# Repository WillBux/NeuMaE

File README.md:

# NeuMaE
Cue Stick for Neuromakers

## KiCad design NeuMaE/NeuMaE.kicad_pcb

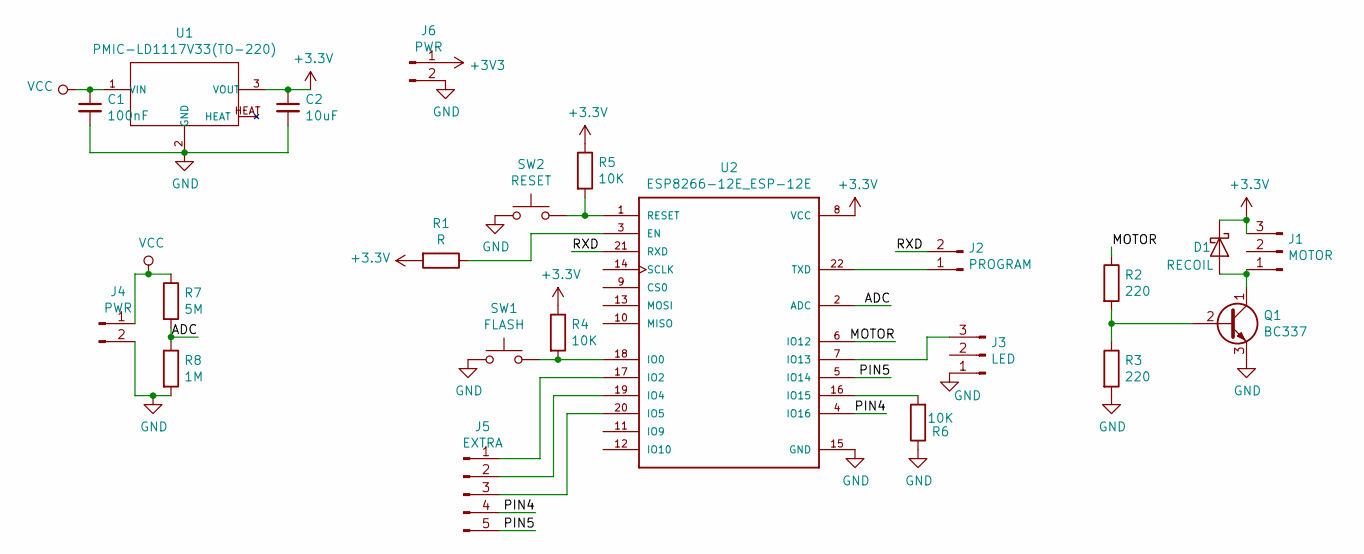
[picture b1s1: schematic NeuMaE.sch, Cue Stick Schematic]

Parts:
C1: 100nF; C_Rect_L7.2mm_W2.5mm_P5.00mm_FKS2_FKP2_MKS2_MKP2
C2: 10uF; CP_Radial_D4.0mm_P2.00mm
D1: RECOIL; D_DO-35_SOD27_P2.54mm_Vertical_AnodeUp
J1: MOTOR; PinHeader_1x03_P2.54mm_Vertical
J2: PROGRAM; PinHeader_1x02_P2.54mm_Vertical
J3: LED; PinHeader_1x03_P2.54mm_Vertical
J4, J6: PWR; PinHeader_1x02_P2.54mm_Vertical
J5: EXTRA; PinHeader_1x05_P2.54mm_Vertical
Q1: BC337; TO-92_Inline
R1: R; R_Axial_DIN0207_L6.3mm_D2.5mm_P10.16mm_Horizontal
R2, R3: 220; R_Axial_DIN0207_L6.3mm_D2.5mm_P10.16mm_Horizontal
R4, R5, R6: 10K; R_Axial_DIN0207_L6.3mm_D2.5mm_P10.16mm_Horizontal
R7: 5M; R_Axial_DIN0207_L6.3mm_D2.5mm_P10.16mm_Horizontal
R8: 1M; R_Axial_DIN0207_L6.3mm_D2.5mm_P10.16mm_Horizontal
SW1: FLASH; SW_PUSH_6mm
SW2: RESET; SW_PUSH_6mm
U1: PMIC-LD1117V33(TO-220); TO-220
U2: ESP8266-12E_ESP-12E; XCVR_ESP8266-12E/ESP-12E

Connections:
/ADC: R7.2, R8.1, U2.2 (ADC)
/MOTOR: R2.1, U2.6 (IO12)
/PIN4: J5.4, U2.4 (IO16)
/PIN5: J5.5, U2.5 (IO14)
/RXD: J2.2, U2.21 (RXD)
GND: C1.2, C2.2, J3.1, J4.2, J6.2, Q1.3 (E), R3.2, R6.1, R8.2, SW1.1, SW2.1, U1.2 (GND), U2.15 (GND)
unnamed: D1.2 (A), J1.1, Q1.1 (C)
unnamed: J2.1, U2.22 (TXD)
unnamed: J3.3, U2.7 (IO13)
unnamed: J5.1, U2.17 (IO2)
unnamed: J5.2, U2.19 (IO4)
unnamed: J5.3, U2.20 (IO5)
unnamed: Q1.2 (B), R2.2, R3.1
unnamed: R1.1, U2.3 (EN)
unnamed: R4.2, SW1.2, U2.18 (IO0)
unnamed: R5.2, SW2.2, U2.1 (RESET)
unnamed: R6.2, U2.16 (IO15)
VCC: C1.1, J4.1, R7.1, U1.1 (VIN)

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
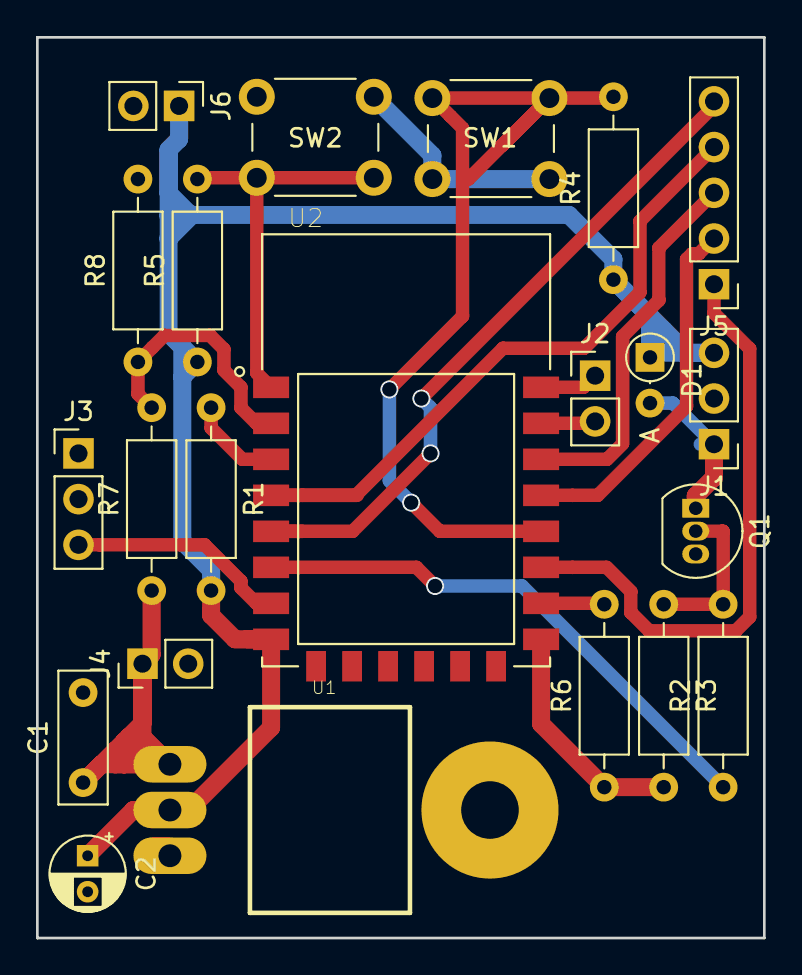
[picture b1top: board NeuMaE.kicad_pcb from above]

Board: 2 copper layers, 40.4 x 50.0 mm, 22 parts (0 on the bottom side), 19 nets.

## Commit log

2020-03-02 arduino code
2020-03-03 added battery voltage
2020-03-04 create pcb
2020-03-04 gerber files
2020-03-04 update gerber
2020-03-04 made board smaller
2020-03-05 fixed C1 footprint
2020-03-05 fixed wdt issue
2020-03-06 added recoil diode
2020-03-11 made even smaller pcb by putting voltage regulator on other side
